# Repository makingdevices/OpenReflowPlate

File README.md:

<!-- Improved compatibility of back to top link: See: https://github.com/othneildrew/Best-README-Template/pull/73 -->

<!--
*** Thanks for checking out the Best-README-Template. If you have a suggestion
*** that would make this better, please fork the repo and create a pull request
*** or simply open an issue with the tag "enhancement".
*** Don't forget to give the project a star!
*** Thanks again! Now go create something AMAZING! :D
-->

<!-- PROJECT SHIELDS -->
<!--
*** I'm using markdown "reference style" links for readability.
*** Reference links are enclosed in brackets [ ] instead of parentheses ( ).
*** See the bottom of this document for the declaration of the reference variables
*** for contributors-url, forks-url, etc. This is an optional, concise syntax you may use.
*** https://www.markdownguide.org/basic-syntax/#reference-style-links
-->
[![Instagram][ig-shield]][ig-url]
[![PCBWAY][sponsor-shield]][sponsor-url]
[![Stargazers][stars-shield]][stars-url]
[![Issues][issues-shield]][issues-url]
[![LinkedIn][linkedin-shield]][linkedin-url]

<!-- PROJECT LOGO -->
<br />
<div align="center">

<h3 align="center">Making Devices</h3>

  <p align="center">
    Open Source projects where we struggle with engineering, electronics, coding and who knows what else... In this case, OpenReflowPlate is a simple reflow plate for SMD PCBs, so hopefully you may find it interesting ;)
  </p>
</div>

<!-- TABLE OF CONTENTS -->
<details>
  <summary>Table of Contents</summary>
  <ol>
    <li>
      <a href="#about-the-project">About The Project</a>
      <ul>
        <li><a href="#built-with">Built With</a></li>
      </ul>
    </li>
    <li>
      <a href="#Build-one">Build one</a>
      <ul>
      </ul>
    </li>
    <li><a href="#usage">Usage</a></li>
    <li><a href="#roadmap">Roadmap</a></li>
    <li><a href="#license">License</a></li>
    <li><a href="#contact">Contact</a></li>
    <li><a href="#Sponsor">Sponsor</a></li>
  </ol>
</details>

<!-- ABOUT THE PROJECT -->
## About The Project

[![Bytes Counter Shot][product-screenshot]](https://github.com/makingdevices/OpenReflowPlate)

OpenReflowPlate wants to be a complete controller where you can attach to it any heat plate and create a reflowplate for SMD components and PCBs. Right now, it is in prototype stage as I do not even have a PCB layout, just testing the capabilities with an expansion board from my Thermo-Logger-Device project. The microcontroller will be the PIC18F45k50.

This device is under development, so I do encourage you to not assembly, order any PCB or use any software from this repository until the project is finished.

<p align="right">(<a href="#readme-top">back to top</a>)</p>

### Built With

[![Microcontroller][PIC]][PIC-url]
[![MPLAB C][MPLAB-C]][MPLAB-C-url]
[![Kicad][kicad-shield]][kicad-url]
[![SPONSOR][sponsor-icon]][sponsor-url]

<p align="right">(<a href="#readme-top">back to top</a>)</p>

<!-- GETTING STARTED -->

## Build one
NOT RECOMMENDED AS THE DEVICE IS UNDER DEVELOPMENT

<p align="right">(<a href="#readme-top">back to top</a>)</p>

<!-- USAGE EXAMPLES -->
## Usage

Instructions of use:

- Only one MAX31855KASA is in use.
- I use the LED output to activate an SSR to control the heat plate.

<p align="right">(<a href="#readme-top">back to top</a>)</p>

<!-- ROADMAP -->
## Roadmap

- [ ] Validate the product with the expansion board and the thermo logger device.
- [ ] Finish the Python software to control the heatplate.
- [ ] Start/finish the new PCB
    - [ ] PIC18F45k50.
    - [ ] Add 8 segment display.
    - [ ] Add buttons for standalone mode.
    - [ ] Develop the PID strategy inside the firmware of the microcontroller.
    - [ ] Isolated USB communication to avoid any damage to the PC if in use. 
- [ ] Test/Validate the project.

See the [open issues](https://github.com/makingdevices/OpenReflowPlate/issues) for a full list of proposed features (and known issues).

State: Project <b>UNFINISHED</b> - 06/01/2023

<p align="right">(<a href="#readme-top">back to top</a>)</p>

<!-- LICENSE -->
## License

Distributed under three licenses:
- [Hardware](/License/HW_cern_ohl_s_v2.pdf)
- [Software](/License/SW_GPLv3.0.txt)
- [Documentation](/License/Documentation_CC-BY-SA-4.0.txt)

[![GPL v3 License][license-shield]][license-url] 
<p align="right">(<a href="#readme-top">back to top</a>)</p>

<!-- CONTACT -->
## Contact

Making Devices - [@MakingDevices](https://www.instagram.com/makingdevices/)

Project Link: [https://github.com/makingdevices/OpenReflowPlate](https://github.com/makingdevices/OpenReflowPlate/)

Other Links: [LinkTree](https://makingdevices.com/links/)

<p align="right">(<a href="#readme-top">back to top</a>)</p>

## Sponsor

[PCBWAY](https://www.pcbway.com/?from=makingdevices) is the most professional PCB manufacturer for prototyping and low-volume production to work with in the world. With more than a decade in the field, They are committed to meeting the needs of their customers from different industries in terms of quality, delivery, cost-effectiveness and any other demanding requests. As Sponsor of Making Devices, they will be in charge of all the PCBs for MDV, allowing both of us to grow together in a long term partnership. We hope you take them into account for your both personal and professional prototypes or products.

[![Sponsor Shot][sponsor-pcb-1]][sponsor-url]
[![Sponsor Shot][sponsor-pcb-2]][sponsor-url]

<!-- MARKDOWN LINKS & IMAGES -->
<!-- https://www.markdownguide.org/basic-syntax/#reference-style-links -->
[contributors-shield]: https://img.shields.io/github/contributors/makingdevices/OpenReflowPlate.svg?style=for-the-badge
[contributors-url]: https://github.com/makingdevices/OpenReflowPlate/graphs/contributors
[forks-shield]: https://img.shields.io/github/forks/makingdevices/OpenReflowPlate.svg?style=for-the-badge
[forks-url]: https://github.com/makingdevices/OpenReflowPlate/network/members
[stars-shield]: https://img.shields.io/github/stars/makingdevices/OpenReflowPlate.svg?style=for-the-badge
[stars-url]: https://github.com/makingdevices/OpenReflowPlate/stargazers
[issues-shield]: https://img.shields.io/github/issues/makingdevices/OpenReflowPlate.svg?style=for-the-badge
[issues-url]: https://github.com/makingdevices/OpenReflowPlate/issues
[license-shield]: /images/license.png
[license-url]: https://github.com/makingdevices/OpenReflowPlate/tree/main/License
[linkedin-shield]: https://img.shields.io/badge/-LinkedIn-black.svg?style=for-the-badge&logo=linkedin&colorB=555
[linkedin-url]: https://www.linkedin.com/company/making-devices/
[sponsor-shield]: https://img.shields.io/badge/SPONSOR-PCBWAY-black.svg?style=for-the-badge&colorB=1200
[sponsor-url]: https://www.pcbway.com/?from=makingdevices
[sponsor-screenshot]: /images/PCB_sponsor.png
[pcb_pic1]: images/openreflowplate_pcb1.jpg
[pcb_pic2]: images/openreflowplate_pcb2.jpg
[product-screenshot]: images/screenshot.jpg
[PIC]: https://img.shields.io/badge/PIC18LF45K50-000000?style=for-the-badge
[PIC-url]: http://ww1.microchip.com/downloads/en/devicedoc/40001350f.pdf
[kicad-shield]: https://img.shields.io/badge/kicad-0b03fc?style=for-the-badge&logo=kicad&logoColor=white
[kicad-url]: https://www.kicad.org/
[YT-screenshot]: images/YT_assembly.PNG
[sponsor-icon]:  https://img.shields.io/badge/-PCBWAY-black.svg?style=for-the-badge&colorB=1200
[ig-shield]: https://img.shields.io/badge/instagram-a83297?style=for-the-badge&logo=instagram&logoColor=white
[ig-url]: https://www.instagram.com/makingdevices/
[MPLAB-C]: https://img.shields.io/badge/MPLAB%20C18-DD0031?style=for-the-badge&logo=C&logoColor=white
[MPLAB-C-url]: https://www.microchip.com/en-us/development-tool/SW006011
[Svelte.dev]: https://img.shields.io/badge/Svelte-4A4A55?style=for-the-badge&logo=svelte&logoColor=FF3E00
[Svelte-url]: https://svelte.dev/
[Laravel.com]: https://img.shields.io/badge/Laravel-FF2D20?style=for-the-badge&logo=laravel&logoColor=white
[Laravel-url]: https://laravel.com
[Bootstrap.com]: https://img.shields.io/badge/Bootstrap-563D7C?style=for-the-badge&logo=bootstrap&logoColor=white
[Bootstrap-url]: https://getbootstrap.com
[JQuery.com]: https://img.shields.io/badge/jQuery-0769AD?style=for-the-badge&logo=jquery&logoColor=white
[JQuery-url]: https://jquery.com

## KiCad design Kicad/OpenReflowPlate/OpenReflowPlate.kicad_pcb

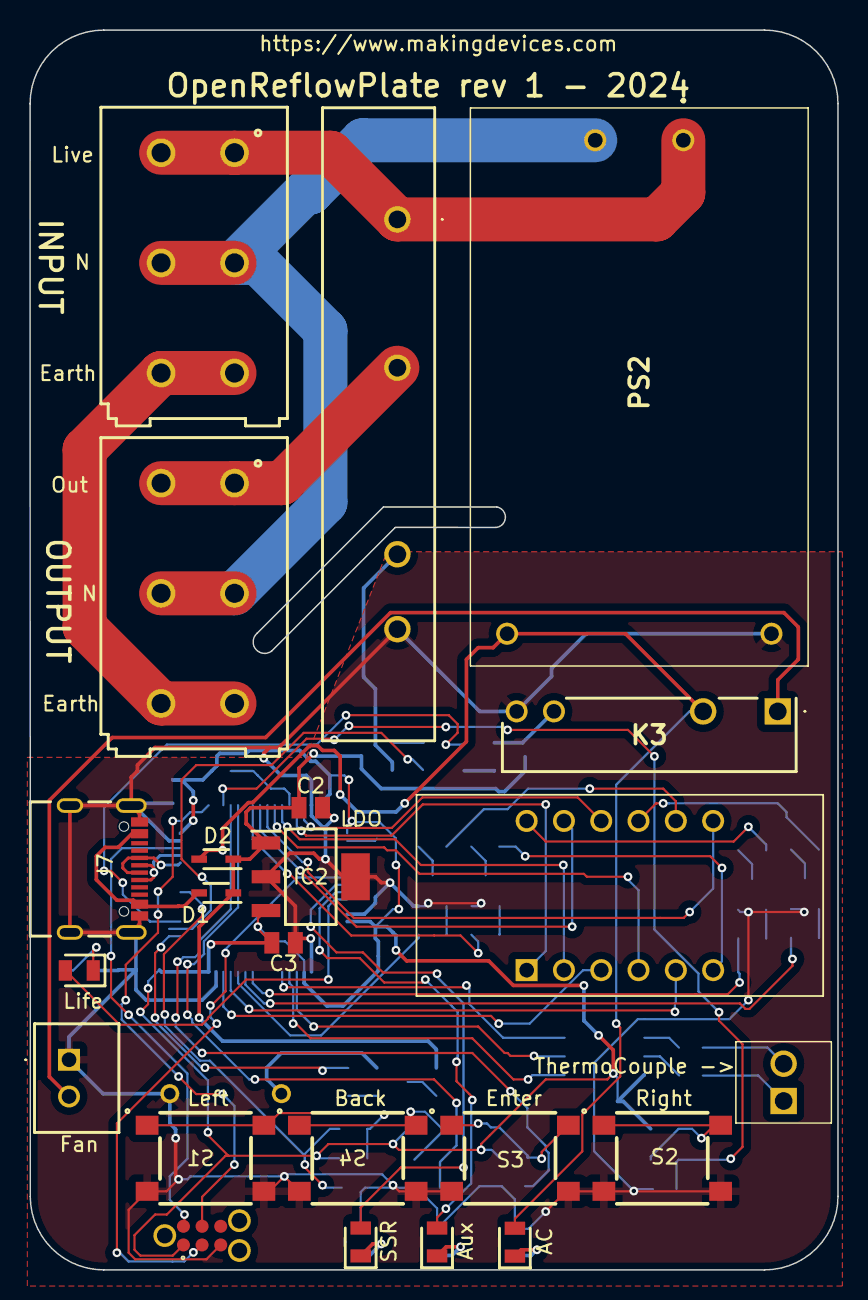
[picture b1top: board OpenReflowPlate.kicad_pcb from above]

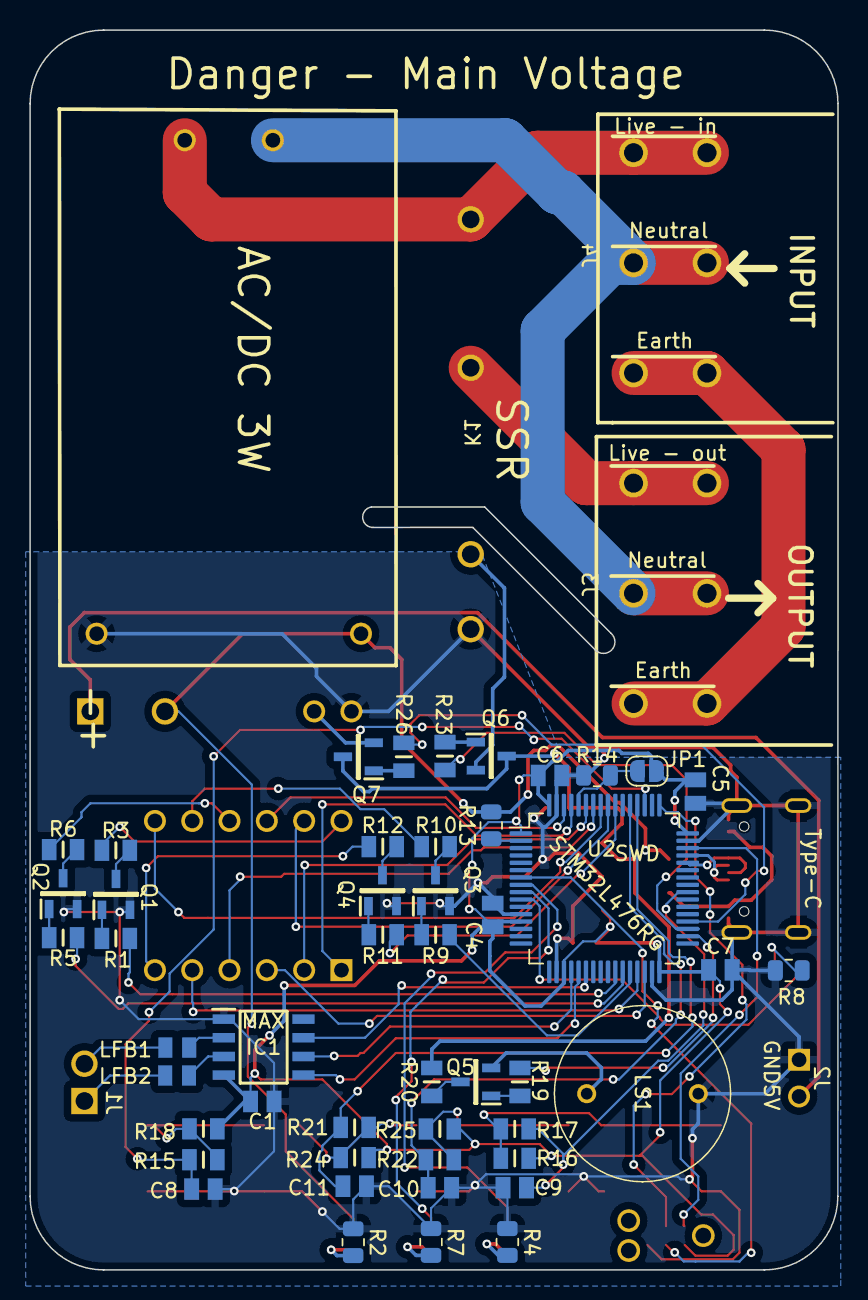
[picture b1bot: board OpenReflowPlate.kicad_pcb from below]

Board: 2 copper layers, 55.0 x 84.4 mm, 71 parts (48 on the bottom side), 73 nets.

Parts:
C1, C2, C3, C5, C6, C7: 100nF; CAPC2012X140N
C4: 4u7; CAPC2012X140N
C8, C9, C10, C11: 22pF; CAPC2012X140N
D1, D2: ZLLS410TA; SOD2513X120N
IC1: MAX31855KASA+; SOIC127P600X175-8N
IC2: TC1108-3.3VDBTR; SOT230P700X180-4N
J1: TC connector; 282834-2_1
J2: B2B-XH-A; B2BXHA
J3: Output_AC; 691411910003
J4: Input_AC; 691411910003
J6: TC2030-MCP-NL
J7: 629722000214
JP1: SolderJumper_2_Open; SolderJumper-2_P1.3mm_Open_RoundedPad1.0x1.5mm
K1: SSRC-240D5R; SSRC240D5R
K3: HF49FD_012-1H11F; HF49FD0121H11F
LED1, LED2, LED3, LED4: SML-H12V8TT86; LEDC2012X90N
LFB1, LFB2: Ferrite; CAPC2012X90N
LS1: TMB12A05
PS2: HLK-5M05; HLK5M05
Q1, Q2, Q3, Q4, Q5, Q6, Q7: SMMBT5551LT1G; SOT96P237X111-3N
R1, R5, R9, R11, R19, R23, R26: 4k7; RESC2012X65N
R2: 1k; R_0805_2012Metric
R3, R6, R10, R12: 100; RESC2012X65N
R4, R7, R8: 220; R_0805_2012Metric
R13: 0; R_0805_2012Metric
R14: 10K; R_0805_2012Metric
R15, R16, R22: 10k; RESC2012X75N
R17: 10K; RESC2012X65N
R18, R24, R25: 10k; RESC2012X65N
R20: 220; RESC2012X65N
R21: 10K; RESC2012X75N
S1: Left Button; 430182070816
S2: Right Button; 430182070816
S3: Enter Button; 430182070816
S4: Back Button; 430182070816
U1: CC56-12EWA; CA56-12EWA
U2: STM32L476RGTx; LQFP-64_10x10mm_P0.5mm

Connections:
+3V3: C1.1, C3.1, C4.2, C5.2, C6.2, C7.2, IC1.4 (VCC), IC2.3 (VOUT), J6.1 (-MCLR/VPP), JP1.1 (A), R16.2, R18.2, R24.2, R25.2, U2.1 (VBAT), U2.13 (VDDA), U2.19 (VDD), U2.32 (VDD), U2.48 (VDDUSB), U2.64 (VDD)
+5V: C2.1, D1.1, D2.1, IC2.1 (VIN), Q6.3, Q7.3, R20.1
AC_L: J4.1, J4.A1, K1.1 (AC_LOAD_1), PS2.1 (AC_1)
AC_N: J3.2, J3.A2, J4.2, J4.A2, PS2.2 (AC_2)
AC_Vdcin+: D2.2, K3.2 (NO), LED1.2, PS2.4 (+VO), R13.2
AC_ground: J3.3, J3.A3, J4.3, J4.A3
Activation_out1: K1.3 (+DC_INPUT), Q6.2
Activation_out2: K3.3 (COIL_1), Q7.2
BUT_BACK: C10.1, R22.1, U2.53 (PC12)
BUT_ENTER: C11.1, R21.1, U2.52 (PC11)
BUT_LEFT: C9.2, R17.2, U2.40 (PC9)
BUT_RIGHT: C8.1, R15.1, U2.51 (PC10)
CC_1: R3.2, U1.12 (CC1)
CC_2: R6.2, U1.9 (CC2)
CC_3: R10.2, U1.8 (CC3)
CC_4: R12.2, U1.6 (CC4)
C_1: R1.1, U2.26 (PB0)
C_2: R5.1, U2.27 (PB1)
C_3: R9.1, U2.28 (PB2)
C_4: R11.1, U2.55 (PB3)
C_buzzer: R19.1, U2.34 (PB13)
C_out1: R23.1, U2.35 (PB14)
C_out2: R26.1, U2.36 (PB15)
DC_Out2: J2.2, K3.1 (COM)
D_a: U1.11 (a), U2.56 (PB4)
D_b: U1.7 (b), U2.57 (PB5)
D_c: U1.4 (c), U2.58 (PB6)
D_d: U1.2 (d), U2.59 (PB7)
D_dp: U1.3 (DPX), U2.30 (PB11)
D_e: U1.1 (e), U2.61 (PB8)
D_f: U1.10 (f), U2.62 (PB9)
D_g: U1.5 (g), U2.29 (PB10)
GND: C1.2, C2.2, C3.2, C4.1, C5.1, C6.1, C7.1, C8.2, C9.1, C10.2, C11.2, IC1.1 (GND), IC2.2 (GND_1), IC2.4 (GND_2), J2.1, J6.5 (PGC_(ICSPCLK)), J7.A1 (GND), J7.A12 (GND1), J7.B1 (GND3), J7.B12 (GND2), J7.S1, J7.S2, J7.S3, J7.S4, K1.4 (_-DC_INPUT), K3.4 (COIL_2), LS1.2 (-), PS2.3 (-VO), Q1.2, Q2.2, Q3.2, Q4.2, R2.1, R4.1, R7.1, R8.1, R14.1, S1.2, S1.4, S2.2, S2.4, S3.2, S3.4, S4.2, S4.4, U2.12 (VSSA), U2.18 (VSS), U2.31 (VSS), U2.47 (VSS), U2.63 (VSS)
LED_LIFE: LED4.2, U2.10 (PC2)
LED_OUT1: LED2.2, U2.8 (PC0)
LED_OUT2: LED3.2, U2.9 (PC1)
unnamed: IC1.3 (T+), LFB2.2
unnamed: IC1.2 (T-), LFB1.2
unnamed: J1.1, LFB2.1
unnamed: J1.2, LFB1.1
unnamed: JP1.2 (B), R14.2, U2.60 (BOOT0)
unnamed: J3.1, J3.A1, K1.2 (AC_LOAD_2)
unnamed: LED1.1, R2.2
unnamed: LED2.1, R4.2
unnamed: LED3.1, R7.2
unnamed: LED4.1, R8.2
unnamed: LS1.1 (+), Q5.2
unnamed: Q1.1, R1.2
unnamed: Q1.3, R3.1
unnamed: Q2.1, R5.2
unnamed: Q2.3, R6.1
unnamed: Q3.1, R9.2
unnamed: Q3.3, R10.1
unnamed: Q4.1, R11.2
unnamed: Q4.3, R12.1
unnamed: Q5.1, R19.2
unnamed: Q5.3, R20.2
unnamed: Q6.1, R23.2
unnamed: Q7.1, R26.2
unnamed: R15.2, R18.1, S2.1, S2.3
unnamed: R16.1, R17.1, S1.1, S1.3
unnamed: R21.2, R24.1, S3.1, S3.3
unnamed: R22.2, R25.1, S4.1, S4.3
unnamed: R13.1, U2.2 (PC13)
SPI1_NSS: IC1.6 (~CS), U2.20 (PA4)
SPI_CLK: IC1.5 (SCK), U2.21 (PA5)
SPI_MISO: IC1.7 (SO), U2.22 (PA6)
SWCLK: J6.4 (PGD_(ICSPDAT)), U2.49 (PA14)
SWDIO: J6.2 (VDD), U2.46 (PA13)
USB_D+: J7.A6 (D+1), J7.B6 (D+2), U2.45 (PA12)
USB_D-: J7.A7 (D-1), J7.B7 (D-2), U2.44 (PA11)
USB_Vin+: D1.2, J7.A4 (VBUS), J7.A9 (VBUS1), J7.B4 (VBUS3), J7.B9 (VBUS2)
reset: J6.3 (GND), U2.7 (NRST)

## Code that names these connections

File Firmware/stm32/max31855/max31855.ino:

#define TIMER_INTERRUPT_DEBUG         0
#define _TIMERINTERRUPT_LOGLEVEL_     0

#include "STM32TimerInterrupt.h"
#include "STM32_ISR_Timer.h"
// inslude the SPI library:
#include <SPI.h>
#include <SoftwareSerial.h>

#define TIMER_INTERVAL_MS         100
#define HW_TIMER_INTERVAL_MS      50

// Init STM32 timer TIM1
STM32Timer ITimer(TIM1);

// Init STM32_ISR_Timer
// Each STM32_ISR_Timer can service 16 different ISR-based timers
STM32_ISR_Timer ISR_Timer;

#define TIMER_INTERVAL_0_50mS         1L
#define TIMER_INTERVAL_0_5S           500L
#define TIMER_INTERVAL_1S             1000L
#define TIMER_INTERVAL_1_5S           1500L
#define DELAYVAL 500

//For display:
int digit_display = 0; //Display digit at the moment 
char const vector[] = {0b00111111,0b00000110,0b01011011,0b01001111,0b01100110,0b01101101,0b01111101,0b00000111,0b01111111,0b01100111,0b001000000,0b01111001}; //Numbers 8-segment codification
char const vector_menu[3][4] = {{0b01101101,0b00111111,0b00111000,0b00111111},{0b01110111,0b00011100,0b00110001,0b00111111},{0b01000000,0b01110011,0b00111001,0b01000000}};  // SOLO, AUTO, PC
int number_display[] = {0,0,0,0}; //Number Storage
int temperature = 0;

// set pin 10 as the slave select for the digital pot:
const int slaveSelectPin = PA4;
const int led_life = PC2;
const int bt_left = PC9;
const int bt_right = PC10;
const int bt_back = PC12;
const int bt_enter = PC11;
const int displayPins[] = {PB4,PB5,PB6,PB7,PB8,PB9,PB10,PB11};
int mode = 0; // 0 = menu, 1 = activated
int menu = 0; // 0 = FIX, 1 = AUTO, 2 = PC.
int menu_lvl = 0; // 0 first lvl, 1 to set temperature

void TimerHandler()
{
  ISR_Timer.run();
}

void inttotemp(int temp){
  number_display[3] = temp % 10;
  number_display[2] = (temp / 10) % 10;
  number_display[1] = (temp / 100) % 10;
  number_display[0] = (temp / 1000) % 10;
}

int nr_digit(int digit){
  		switch(digit){  //Print the numbers over the display
			case 3:		//we light the correct display
				digitalWrite(PB0, LOW);
        digitalWrite(PB1, LOW);
        digitalWrite(PB2, LOW);
        digitalWrite(PB3, HIGH);
				digit = 0;
				break;
			case 0:
				digitalWrite(PB0, HIGH);
        digitalWrite(PB1, LOW);
        digitalWrite(PB2, LOW);
        digitalWrite(PB3, LOW);
				digit = 1;
				break;
			case 1:
				digitalWrite(PB0, LOW);
        digitalWrite(PB1, HIGH);
        digitalWrite(PB2, LOW);
        digitalWrite(PB3, LOW);
				digit = 2;
				break;
			case 2:
				digitalWrite(PB0, LOW);
        digitalWrite(PB1, LOW);
        digitalWrite(PB2, HIGH);
        digitalWrite(PB3, LOW);
				digit = 3;
				break;
			default:
				break;
		}
    return digit;
}

void print_display(int number){
  for(int i=0;i<8;i++) {
    digitalWrite(displayPins[i], (vector[number]&(0b00000001<<i))>>i);
  }
}

void print_menu_display(int number){
  for(int i=0;i<8;i++) {
    digitalWrite(displayPins[i], (vector_menu[menu-1][number]&(0b00000001<<i))>>i);
  }
}

int buttonstate = 0;  // variable for reading the pushbutton status
void TimerInterrupt()
{
  if(mode==1 || (mode==0 && menu == 0)){
    inttotemp(temperature);
    print_display(number_display[digit_display]);
  } else {
    print_menu_display(digit_display);
  }
  digit_display = nr_digit(digit_display);

  if(digitalRead(bt_right) == LOW && buttonstate==0){
    buttonstate=1;
    if(menu_lvl==0 && menu < 3) menu++;
    else if(menu_lvl==0) menu = 0;
  }
  if(digitalRead(bt_left) == LOW && buttonstate==0){
    buttonstate=1;
    if(menu_lvl==0 && menu > 0) menu--;
    else if(menu_lvl==0) menu = 3;
  }
  if(digitalRead(bt_back) == LOW && buttonstate==0){
    buttonstate=1;
    menu = 0;
  }
  if(digitalRead(bt_right) == HIGH && digitalRead(bt_left) == HIGH && digitalRead(bt_back) == HIGH){
    buttonstate=0;
  }
}
// Create a new SPI port with:
// Pin 2 = MOSI,
// Pin 3 = MISO,
// Pin 4 = SCK
// Set up a new SoftwareSerial object
void setup() {
  // open the serial port at 9600 bps:
  //Serial.begin(9600);
  
  SPI.begin();
  // set the slaveSelectPin as an output:
  pinMode(slaveSelectPin, OUTPUT);
  pinMode(PB0, OUTPUT);
  pinMode(PB1, OUTPUT);
  pinMode(PB2, OUTPUT);
  pinMode(PB3, OUTPUT);
  pinMode(PB14, OUTPUT);
  pinMode(PB15, OUTPUT);

  pinMode(bt_left, INPUT);
  pinMode(bt_right, INPUT);
  pinMode(bt_back, INPUT);
  pinMode(bt_enter, INPUT);
  
  for(int i=0;i<8;i++) {
    pinMode(displayPins[i], OUTPUT);
  }
  pinMode(led_life, OUTPUT);
  // Interval in microsecs
  if (ITimer.attachInterruptInterval(HW_TIMER_INTERVAL_MS * 100, TimerHandler))
  {
    
  }

  // Just to demonstrate, don't use too many ISR Timers if not absolutely necessary
  // You can use up to 16 timer for each ISR_Timer
  ISR_Timer.setInterval(TIMER_INTERVAL_0_50mS,  TimerInterrupt);
}

int incomingByte = 0;
void loop() {
  // go through the six channels of the digital pot:
  temperature = MAX31855K();
  delay(DELAYVAL);
  digitalWrite(led_life, !digitalRead(led_life));
  digitalWrite(PB14, HIGH);
  digitalWrite(PB15, HIGH);
  //Serial.print(" External_temp: ");
  //Serial.println(temperature);
}

int MAX31855K(void) {
  int var1=0, var2=0, var3=0, var4=0, var5= 0;
  double external_temp = 0;
  double internal_temp = 0;

  // take the SS pin low to select the chip:
  digitalWrite(slaveSelectPin, LOW);
  delay(500);
  var1 = SPI.transfer(0xFF);
  var2 = SPI.transfer(0xFF);
  var3 = SPI.transfer(0xFF);
  var4 = SPI.transfer(0xFF);
  var5 = SPI.transfer(0xFF);
  // take the SS pin high to de-select the chip:
  digitalWrite(slaveSelectPin, HIGH);
  /*
  Serial.println("Let's begin");
  Serial.println(var1);
  Serial.println(var2);
  Serial.println(var3);
  Serial.println(var4);
  Serial.println(var5);
*/
  internal_temp = (var3<<4) | (var4&0xF0)>>4;
  internal_temp = internal_temp*0.0625;
  external_temp = var1<<6 | (var2&0b11111100)>>2;
  external_temp = external_temp * 0.25;

  return external_temp;
}

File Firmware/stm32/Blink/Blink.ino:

/*
  Blink

  Turns an LED on for one second, then off for one second, repeatedly.

  Most Arduinos have an on-board LED you can control. On the UNO, MEGA and ZERO
  it is attached to digital pin 13, on MKR1000 on pin 6. LED_BUILTIN is set to
  the correct LED pin independent of which board is used.
  If you want to know what pin the on-board LED is connected to on your Arduino
  model, check the Technical Specs of your board at:
  https://www.arduino.cc/en/Main/Products

  modified 8 May 2014
  by Scott Fitzgerald
  modified 2 Sep 2016
  by Arturo Guadalupi
  modified 8 Sep 2016
  by Colby Newman

  This example code is in the public domain.

  https://www.arduino.cc/en/Tutorial/BuiltInExamples/Blink
*/

// the setup function runs once when you press reset or power the board
void setup() {
  // initialize digital pin LED_BUILTIN as an output.
  pinMode(PC0, OUTPUT);
  pinMode(PC1, OUTPUT);
  pinMode(PC2, OUTPUT);
  pinMode(PC13, OUTPUT);
  pinMode(PC9, INPUT);
  pinMode(PC10, INPUT);
  pinMode(PC12, INPUT);
}

int buttonState_left = 0;
int buttonState_right = 0;
int buttonState_back = 0;

// the loop function runs over and over again forever
void loop() {
  buttonState_left = digitalRead(PC9);
  buttonState_right = digitalRead(PC10);
  buttonState_back = digitalRead(PC12);
  if(buttonState_left == LOW){
    digitalWrite(PC0, HIGH);  // turn the LED on (HIGH is the voltage level)
  } else {
     digitalWrite(PC0, LOW); 
  }
  if(buttonState_right == LOW){
    digitalWrite(PC1, HIGH);  // turn the LED on (HIGH is the voltage level)
  } else {
     digitalWrite(PC1, LOW); 
  }
  if(buttonState_back == LOW){
    digitalWrite(PC13, HIGH);  // turn the LED on (HIGH is the voltage level)
  } else {
     digitalWrite(PC13, LOW); 
  }
  digitalWrite(PC2, HIGH);  // turn the LED on (HIGH is the voltage level)
  delay(100); 
  
  buttonState_left = digitalRead(PC9);
  if(buttonState_left == LOW){
    digitalWrite(PC0, HIGH);  // turn the LED on (HIGH is the voltage level)
  } else {
     digitalWrite(PC0, LOW); 
  }
    if(buttonState_right == LOW){
    digitalWrite(PC1, HIGH);  // turn the LED on (HIGH is the voltage level)
  } else {
     digitalWrite(PC1, LOW); 
  }            // wait for a second
  if(buttonState_back == LOW){
    digitalWrite(PC13, HIGH);  // turn the LED on (HIGH is the voltage level)
  } else {
     digitalWrite(PC13, LOW); 
  }
  digitalWrite(PC2, LOW);   // turn the LED off by making the voltage LOW
  delay(100);                      // wait for a second
}

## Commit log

2022-12-19 Update New project
2022-12-27 New improvements
2022-12-27 Deleting version on software
2022-12-27 New python Head
2023-01-06 no message
2024-01-04 Rev 0.1
2024-09-05 last version
2024-09-05 New PCBs!
2024-12-10 V1 HW
